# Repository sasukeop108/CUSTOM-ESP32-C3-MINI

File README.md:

# CUSTOM-ESP32-C3-MINI
This is an ESP32 development board made using the ESP32-C3-MINI Chip. It has features like lipo battery charging and programming through computer. This looks simple but i had spent approximately 13 hour to make this dev board myself. It hs tp4056 ic inbuilt for charging and esd diodes for protection. The battery could be even charged while programming the devboard because there are diodes to prevent backflow of the current. This was fully developed by me with the help of kicad.
# BOM
# JLCPCB Bill of Materials (BOM)

## Order Summary

- **BOM Name**: bom-JLCPCB Assembly Order (7)
- **PCB Assembled Qty**: 2
- **Est. Total Price**: $12.7414
- **Download Time**: 2026-05-02 21:22:55

## Component List

| Designator | Value | Footprint | Part Number | Manufacturer | Description | Category | Qty | Price |
|---|---|---|---|---|---|---|---|---|
| 1K1 | R | 0402 | 0402WGF1001TCE | UNI-ROYAL(Uniroyal Elec) | -55℃~+155℃ 1kΩ 50V 62.5mW Thick Film Resistor ±1% ±100ppm/℃ 0402 Ch... | Chip Resistor - Surface Mount | 8 | $0.008 |
| R11 | 1.2k | 0402 | 0402WGF1001TCE | UNI-ROYAL(Uniroyal Elec) | -55℃~+155℃ 1kΩ 50V 62.5mW Thick Film Resistor ±1% ±100ppm/℃ 0402 Ch... | Chip Resistor - Surface Mount | 8 | $0.008 |
| R12,R14 | 1k | 0402 | 0402WGF1001TCE | UNI-ROYAL(Uniroyal Elec) | -55℃~+155℃ 1kΩ 50V 62.5mW Thick Film Resistor ±1% ±100ppm/℃ 0402 Ch... | Chip Resistor - Surface Mount | 8 | $0.008 |
| C1,C2,C3,C4 | 47uF | 0805 | CL21A476MQYNNNE | Samsung Electro-Mechanics | 47uF 6.3V X5R ±20% 0805 Multilayer Ceramic Capacitors MLCC - SMD/SM... | Multilayer Ceramic Capacitors MLCC - SMD/SMT | 8 | $0.3048 |
| C5,C6 | 0.1uF | 0402 | CL05B104KO5NNNC | Samsung Electro-Mechanics | 100nF 16V X7R ±10% 0402 Multilayer Ceramic Capacitors MLCC - SMD/SM... | Multilayer Ceramic Capacitors MLCC - SMD/SMT | 8 | $0.0104 |
| C10,C9 | 100nF | 0402 | CL05B104KO5NNNC | Samsung Electro-Mechanics | 100nF 16V X7R ±10% 0402 Multilayer Ceramic Capacitors MLCC - SMD/SM... | Multilayer Ceramic Capacitors MLCC - SMD/SMT | 8 | $0.0104 |
| C7,C8 | 12pF | 0402 | 0402CG120J500NT | FH (Guangdong Fenghua Advanced Tech) | 12pF 50V C0G ±5% 0402 Multilayer Ceramic Capacitors MLCC - SMD/SMT ... | Multilayer Ceramic Capacitors MLCC - SMD/SMT | 4 | $0.0052 |
| C11,C12 | 10uF | 0805 | GRM21BR61H106KE43L | Murata Electronics | 10uF 50V X5R ±10% 0805 Multilayer Ceramic Capacitors MLCC - SMD/SMT... | Multilayer Ceramic Capacitors MLCC - SMD/SMT | 4 | $0.272 |
| D2,D3,D4 | LED | 0402 | 16-213/BHC-AN1P2/3T | Everlight Elec | -40℃~+85℃ 120° 20mA 3.3V 468nm 471nm 50.25mcd 95mW Blue Discrete Di... | LED Indication - Discrete | 20 | $0.572 |
| D5,D6 | D_Schottky | SOD-323 | B5819WS-TP | MCC(Micro Commercial Components) | -65℃~+125℃ 1 Independent 10A 1A 40V 40uA@40V 600mV@1A SOD-323 Schot... | Global Sourcing Parts | 8 | $0.3336 |
| D1_2,D7,D8 | D_TVS_Small | SOD-923 | LESD9D5.0CT5G | LRC | -40℃~+125℃ 150W@8/20us 15pF 18.6V 5.6V 500nA 5V 9.4A@8/20us Bidirec... | ESD And Surge Protection (TVS/ESD) | 20 | $0.452 |
| J1 | USB_C_Receptacle_USB2.0_16P | SMD | TYPE-C-31-M-12 | Korean Hroparts Elec | -30℃~+80℃ 1 10,000 cycles 16P 20V 5A 7.35mm Female Surface Mount, R... | USB Connectors | 2 | $0.3662 |
| R1,R2 | 5.1k | 0402 | 0402WGF5101TCE | UNI-ROYAL(Uniroyal Elec) | -55℃~+155℃ 5.1kΩ 50V 62.5mW Thick Film Resistor ±1% ±100ppm/℃ 0402 ... | Chip Resistor - Surface Mount | 4 | $0.0036 |
| R3 | R | 0805 | 0805W8F1001T5E | UNI-ROYAL(Uniroyal Elec) | -55℃~+155℃ 125mW 150V 1kΩ Thick Film Resistor ±1% ±100ppm/℃ 0805 Ch... | Chip Resistor - Surface Mount | 2 | $0.006 |
| R4 | 10M | 0402 | 0402WGJ0106TCE | UNI-ROYAL(Uniroyal Elec) | -55℃~+155℃ 10MΩ 50V 62.5mW Thick Film Resistor ±100ppm/℃ ±5% 0402 C... | Chip Resistor - Surface Mount | 20 | $0.012 |
| R5 | 100k | 0402 | 0402WGF1003TCE | UNI-ROYAL(Uniroyal Elec) | -55℃~+155℃ 100kΩ 50V 62.5mW Thick Film Resistor ±1% ±100ppm/℃ 0402 ... | Chip Resistor - Surface Mount | 2 | $0.0018 |
| R6,R7,R8,R9 | 10k | 0402 | 0402WGF1002TCE | UNI-ROYAL(Uniroyal Elec) | -55℃~+155℃ 10kΩ 50V 62.5mW Thick Film Resistor ±1% ±100ppm/℃ 0402 C... | Chip Resistor - Surface Mount | 8 | $0.0104 |
| SW1,SW2 | SW_Push | SMD,3.1x2.5mm | GT-TC032A-H015-L1 | G-Switch | -30℃~+85℃ 1.5mm 1.6N 100,000 cycles 12V 2.5mm 3.05mm 50mA Black No ... | Tactile Switches | 5 | $0.9455 |
| U1 | ESP32-C3-WROOM-02 | VFQFN-32-EP | ESP32-C3-WROOM-02-N4 | Espressif Systems | -105dBm -40℃~+85℃ 2.4GHz 20.5dBm 345mA 3V~3.6V 82mA Bluetooth5.0 ES... | WiFi Modules | 2 | $6.1606 |
| U3 | AP2112K-3.3 | SOT-23-5 | AP2112K-3.3TRG1 | TECH PUBLIC | -40℃~+85℃@(Ta) 1 10uA 3.3V 320mV@(600mA) 5.5V 600mA 75dB@(1kHz) Fix... | Voltage Regulators - Linear, Low Drop Out (LDO) Regulators | 5 | $0.533 |
| U4 | TP4056-42-ESOP8 | ESOP-8 | TP4056-42-ESOP8 | TOPPOWER(Nanjing Extension Microelectronics) | -40℃~+85℃ 1 1A 2uA 4.2V 4V~8V Charging IC Lithium Battery Support E... | Battery Management | 0 | $0 |
| Y1 | Crystal | SMD3215-2P | ABS07-32.768KHZ-T | Abracon LLC | -40℃~+85℃ 12.5pF 32.768kHz 70kΩ Crystal Oscillator ±20ppm SMD3215-2... | Crystals | 5 | $2.5165 |
| D1 | PESD5V0L1ULD | DFN1006-2(SOD-882) | PESD5V0L1ULD,315 | Nexperia | -55℃~+150℃ 1 10nA 12V 25pF 3.5A@8/20us 42W 5V 6.4V ESD IEC 61000-4-... | ESD And Surge Protection (TVS/ESD) | 5 | $0.2014 |
# PCB

# CART

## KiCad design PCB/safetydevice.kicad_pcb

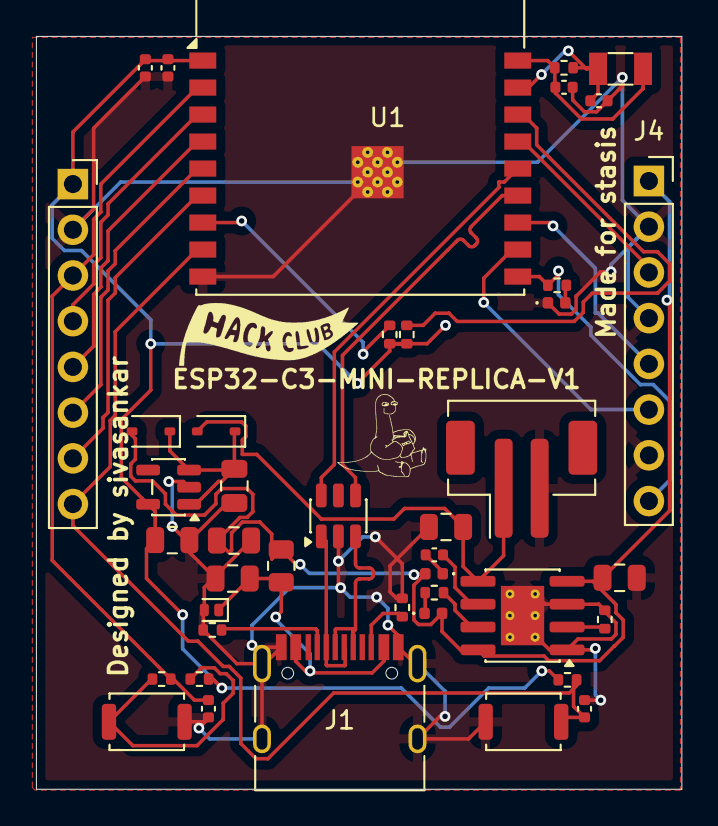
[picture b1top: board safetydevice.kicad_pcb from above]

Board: 2 copper layers, 35.9 x 41.8 mm, 42 parts (0 on the bottom side), 33 nets.

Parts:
1k1: R; C_0402_1005Metric
C1, C2, C3, C4: 47uF; C_0805_2012Metric
C5, C6: 0.1uF; C_0402_1005Metric
C7, C8: 12pF; C_0402_1005Metric
C9, C10: 100nF; C_0402_1005Metric
C11, C12: 10uF; C_0805_2012Metric
D1: PESD5V0L1ULD; D_SOD-882D
D2, D3, D4: LED; LED_0402_1005Metric
D5, D6: D_Schottky; D_SOD-323
J1: USB_C_Receptacle_USB2.0_16P; USB_C_Receptacle_HRO_TYPE-C-31-M-12
J2: BATTERYJST; JST_PH_B2B-PH-SM4-TB_1x02-1MP_P2.00mm_Vertical
J3, J4: Conn_01x08_Pin; PinSocket_1x08_P2.54mm_Vertical
R1, R2: 5.1k; R_0402_1005Metric
R3: R; R_0805_2012Metric
R4: 10M; R_0402_1005Metric
R5: 100k; R_0402_1005Metric
R6, R7, R8, R9: 10k; R_0402_1005Metric
R11: 1.2k; R_0402_1005Metric
R12, R14: 1k; R_0402_1005Metric
SW1, SW2: SW_Push; SW_Push_SPST_NO_Alps_SKRK
U1: ESP32-C3-WROOM-02
U2: USBLC6-2SC6; SOT-23-6
U3: AP2112K-3.3; SOT-23-5
U4: TP4056-42-ESOP8; SOIC-8-1EP_3.9x4.9mm_P1.27mm_EP2.41x3.3mm_ThermalVias
Y1: Crystal; Crystal_SMD_3215-2Pin_3.2x1.5mm

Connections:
+3V3: C4.1, C5.1, C6.1, J3.1, R6.2, R7.2, R8.2, R9.2, U1.1 (3V3), U3.5 (VOUT)
+5V: C2.1, C12.1, D2.2 (A), D3.2 (A), D5.2 (A), J4.1, R3.2, U4.4 (V_{CC}), U4.8 (CE)
/D+: J1.A6 (D+), J1.B6 (D+), U2.3 (I/O2)
/D-: J1.A7 (D-), J1.B7 (D-), U2.1 (I/O1)
BATOUT: C11.1, D6.2 (A), J2.1, U4.5 (BAT)
EN: C9.1, J3.3, R5.2, U1.2 (EN)
GND: C1.2, C2.2, C3.2, C4.2, C5.2, C6.2, C7.2, C8.2, C9.2, C10.2, C11.2, C12.2, D1.2 (A), D4.1 (K), J1.A1 (GND), J1.A12 (GND), J1.B1 (GND), J1.B12 (GND), J1.S1 (SHIELD), J2.2, J3.2, J4.2, J4.4, J4.7, R1.2, R2.2, R11.2, SW1.1, SW2.1, U1.9 (GND), U1.19 (GND), U2.2 (GND), U3.2 (GND), U4.1 (TEMP), U4.3 (GND), U4.9 (EPAD)
IO2: R8.1, U1.16 (IO2)
IO3: J4.3, U1.15 (IO3)
IO4: J3.4, U1.3 (IO4)
IO5: J3.5, U1.4 (IO5)
IO6: J3.6, U1.5 (IO6)
IO7: J3.7, U1.6 (IO7)
IO8: R9.1, U1.7 (IO8)
IO9: C10.1, J3.8, R7.1, SW2.2, U1.8 (IO9)
IO10: J4.8, R14.2, U1.10 (IO10)
unnamed: D2.1 (K), R12.1
unnamed: 1k1.1, D3.1 (K)
unnamed: D4.2 (A), R14.1
unnamed: C3.1, D5.1 (K), D6.1 (K), U3.1 (VIN), U3.3 (EN)
unnamed: J1.A5 (CC1), R1.1
unnamed: J1.B5 (CC2), R2.1
unnamed: R5.1, R6.1, SW1.2
unnamed: C7.1, R4.1, U1.18 (IO0), Y1.1
unnamed: C8.1, R4.2, U1.17 (IO1), Y1.2
unnamed: R11.1, U4.2 (PROG)
unnamed: R12.2, U4.7 (~CHRG)
unnamed: 1k1.2, U4.6 (~STDBY)
RXD: J4.6, U1.11 (IO20/RXD)
TXD: J4.5, U1.12 (IO21/TXD)
USB_D+: U1.14 (IO19), U2.6 (I/O1)
USB_D-: U1.13 (IO18), U2.4 (I/O2)
VBUS: C1.1, D1.1 (K), J1.A4 (VBUS), J1.A9 (VBUS), J1.B4 (VBUS), J1.B9 (VBUS), R3.1

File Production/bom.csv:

Designator,Footprint,Quantity,Value,LCSC Part #
1K1,0402,1,R,
"C1, C2, C3, C4",0805,4,47uF,
"C10, C9",0402,2,100nF,
"C11, C12",0805,2,10uF,
"C5, C6",0402,2,0.1uF,
"C7, C8",0402,2,12pF,
D1,D_SOD-882D,1,PESD5V0L1ULD,
"D2, D3, D4",0402,3,LED,
"D5, D6",D_SOD-323,2,D_Schottky,
J1,USB_C_Receptacle_HRO_TYPE-C-31-M-12,1,USB_C_Receptacle_USB2.0_16P,
J2,JST_PH_B2B-PH-SM4-TB_1x02-1MP_P2.00mm_Vertical,1,BATTERYJST,
"J3, J4",PinSocket_1x08_P2.54mm_Vertical,2,Conn_01x08_Pin,
"R1, R2",0402,2,5.1k,
R11,0402,1,1.2k,
"R12, R14",0402,2,1k,
R3,0805,1,R,
R4,0402,1,10M,
R5,0402,1,100k,
"R6, R7, R8, R9",0402,4,10k,
"SW1, SW2",SW_Push_SPST_NO_Alps_SKRK,2,SW_Push,
U1,ESP32-C3-WROOM-02,1,ESP32-C3-WROOM-02,
U2,SOT-23-6,1,USBLC6-2SC6,
U3,SOT-23-5,1,AP2112K-3.3,
U4,SOIC-8-1EP_3.9x4.9mm_P1.27mm_EP2.41x3.3mm_ThermalVias,1,TP4056-42-ESOP8,
Y1,Crystal_SMD_3215-2Pin_3.2x1.5mm,1,Crystal,

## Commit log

2026-04-12 Create k
2026-04-12 Create S
2026-04-13 Rename safetydevice.zip to custom-esp32-c3.zip
2026-04-13 Update LICENSE
2026-04-13 Rename safetydevice.kicad_pcb to custom-esp32-c3.kicad_pcb
2026-04-13 Add custom ESP32-C3 project file
2026-04-13 Rename custom-esp32-c3_pro to custom-esp32-c3.kicad_pro
2026-04-13 Rename PCB/safetydevice.kicad_sch to custom-esp32-c3.kicad_sch
2026-04-13 Rename safetydevice.png to custom-esp32-c3.png
2026-05-02 Revise development time and enhance README content
    Updated the time spent on development from 8 hours to 13 hours. Added order summary and component list sections.
2026-05-02 Rename safetydevice.kicad_pro to custom-esp32-c3.kicad_pro
2026-05-02 Rename safetydevice.kicad_sch to custom-esp32-c3.kicad_sch
